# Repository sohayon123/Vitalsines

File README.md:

# Vitalsines
 
During my time as a co-op student at Vitalsines, I was responsible for the design and assembly of a variety of mechanical and electrical projects, however, the main project that I worked on was a device with the objective of measuring pulse wave velocity in a comfortable and easy way. 

## PCB Design
I developed 3 different PCBs for this project, one for filtering incoming data from piezo sensors of my design, one for aggregating sensor data lines, and one for sending this data to a DAQ. These PCBs were extremely small, at only 2cm diameter, and were assembled by hand. They contained a adjustable low pass filter to get rid of some of the noise in the analog signal from the piezo. The component size for this PCB was 0603 and the board was designed to have 4 layers, one ground plane and one 10V power plane, to help clean up the traces.

## Mechanical Design

The mechanical design involved creating a strap that would host all of the electronics and sit comfortably on the chest. It also involved the design of some enclosures for the piezo sensors. Below are some pictures of the final result and some of the CAD files. The strap was designed with some areas of varying thickness to allow the PCBs to clip directly into the prototype strap. There were some cavities left in the strap as well to accomodate the various sensor cables.

[Link to Cad Viewer!](https://github.com/sohayon123/Vitalsines/blob/main/CAD/strap.STL)

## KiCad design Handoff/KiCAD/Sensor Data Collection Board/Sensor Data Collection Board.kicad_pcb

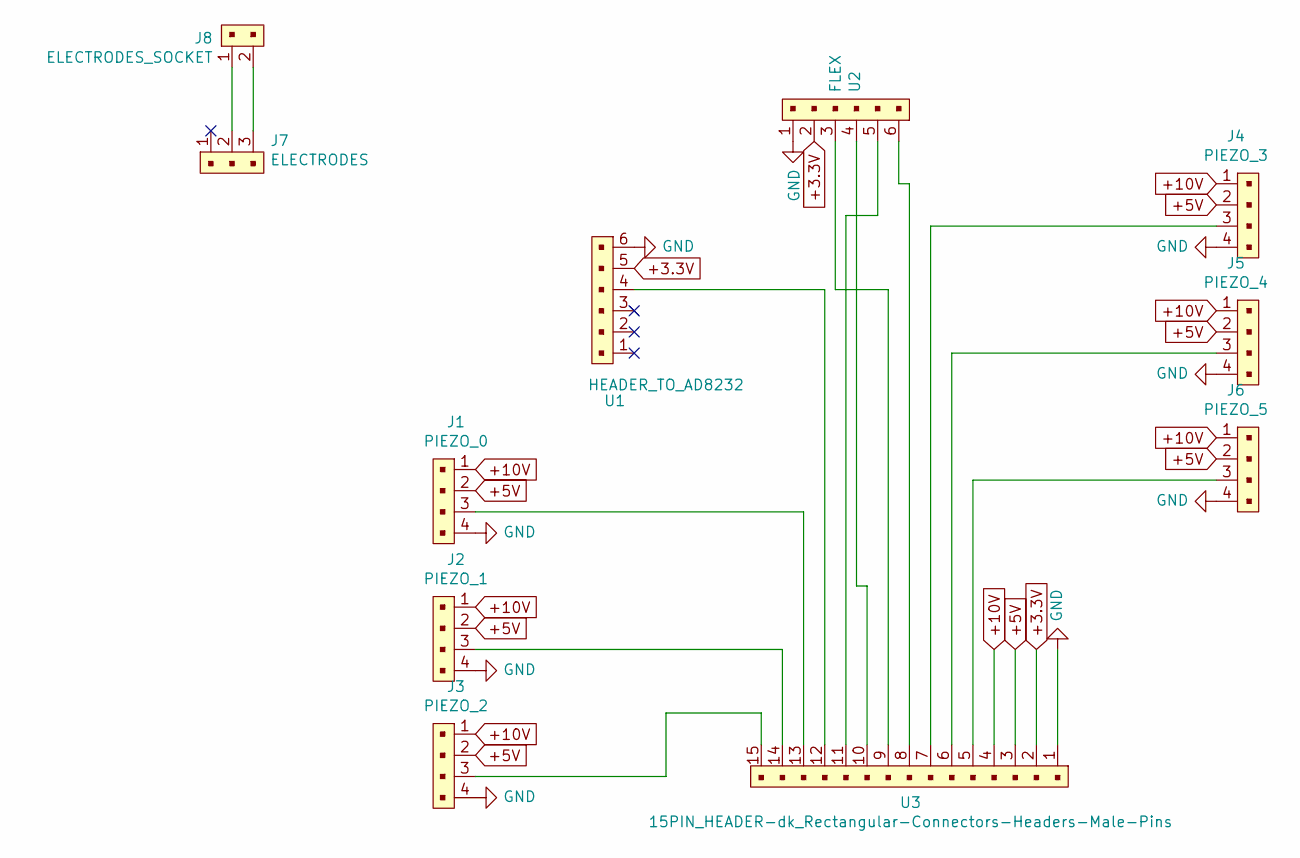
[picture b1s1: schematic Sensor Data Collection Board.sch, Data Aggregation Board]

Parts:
J1: PIEZO_0; BM04B-SRSS-TB; MPN B4B-PH-K-S(LF)(SN); Digi-Key_PN 455-1706-ND
J2: PIEZO_1; BM04B-SRSS-TB; MPN B4B-PH-K-S(LF)(SN); Digi-Key_PN 455-1706-ND
J3: PIEZO_2; BM04B-SRSS-TB; MPN B4B-PH-K-S(LF)(SN); Digi-Key_PN 455-1706-ND
J4: PIEZO_3; BM04B-SRSS-TB; MPN B4B-PH-K-S(LF)(SN); Digi-Key_PN 455-1706-ND
J5: PIEZO_4; BM04B-SRSS-TB; MPN B4B-PH-K-S(LF)(SN); Digi-Key_PN 455-1706-ND
J6: PIEZO_5; BM04B-SRSS-TB; MPN B4B-PH-K-S(LF)(SN); Digi-Key_PN 455-1706-ND
J7: ELECTRODES; PinHeader_1x03_P2.54mm_Vertical; MPN 640456-3; Digi-Key_PN A19470-ND
J8: ELECTRODES_SOCKET; SM02B-SRSS-TB; MPN 22-23-2021; Digi-Key_PN WM4200-ND
U1: HEADER_TO_AD8232; PinHeader_1x06_P2.54mm_Vertical
U2: FLEX; BM06B-SRSS-TB
U3: 15PIN_HEADER-dk_Rectangular-Connectors-Headers-Ma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; DB15 2 row

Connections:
+3.3V: U1.5, U2.2, U3.2
+5V: J1.2, J2.2, J3.2, J4.2, J5.2, J6.2, U3.3
+10V: J1.1, J2.1, J3.1, J4.1, J5.1, J6.1, U3.4
GND: J1.4, J2.4, J3.4, J4.4, J5.4, J6.4, U1.6, U2.1, U3.1
unnamed: J1.3, U3.13
unnamed: J2.3, U3.14
unnamed: J3.3, U3.15
unnamed: J4.3, U3.7
unnamed: J5.3, U3.6
unnamed: J6.3, U3.5
unnamed: J7.2, J8.1
unnamed: J7.3, J8.2
unnamed: U1.4, U3.12
unnamed: U2.3, U3.9
unnamed: U2.4, U3.10
unnamed: U2.5, U3.11
unnamed: U2.6, U3.8

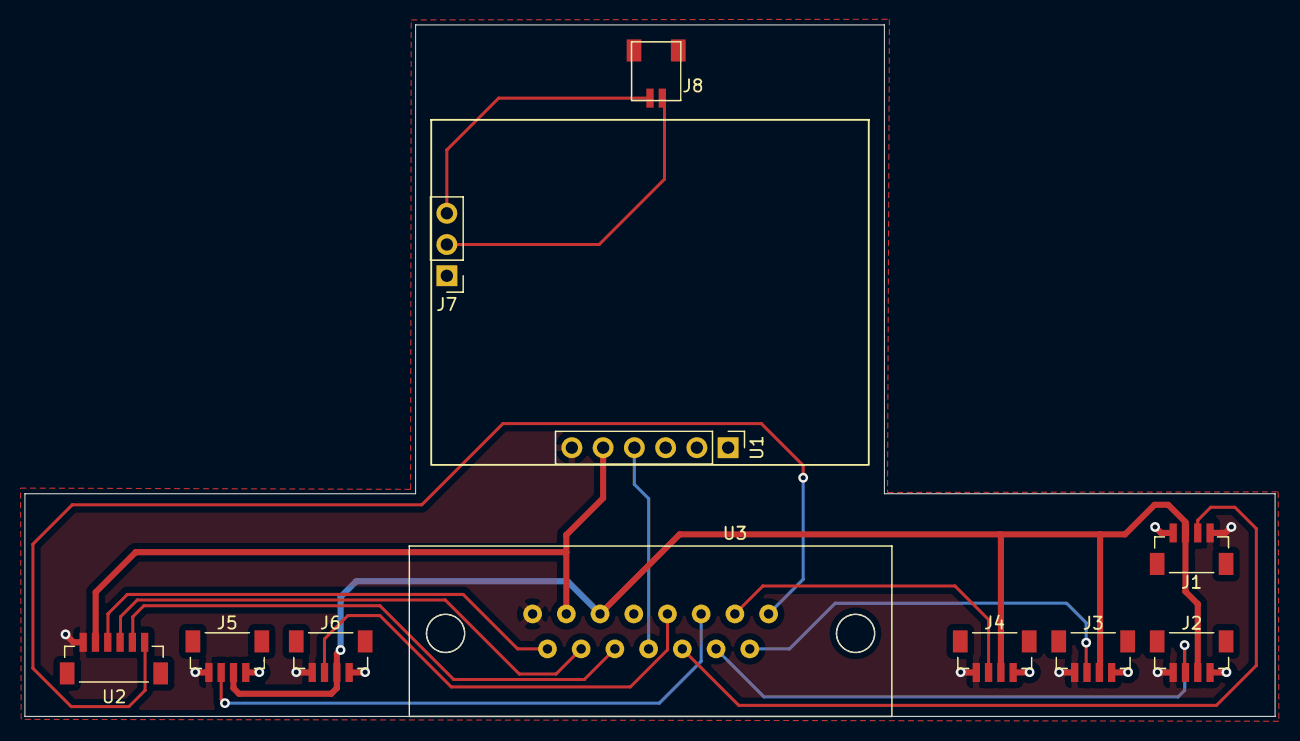
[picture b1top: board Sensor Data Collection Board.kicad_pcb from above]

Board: 4 copper layers, 101.6 x 56.2 mm, 11 parts (0 on the bottom side), 17 nets.

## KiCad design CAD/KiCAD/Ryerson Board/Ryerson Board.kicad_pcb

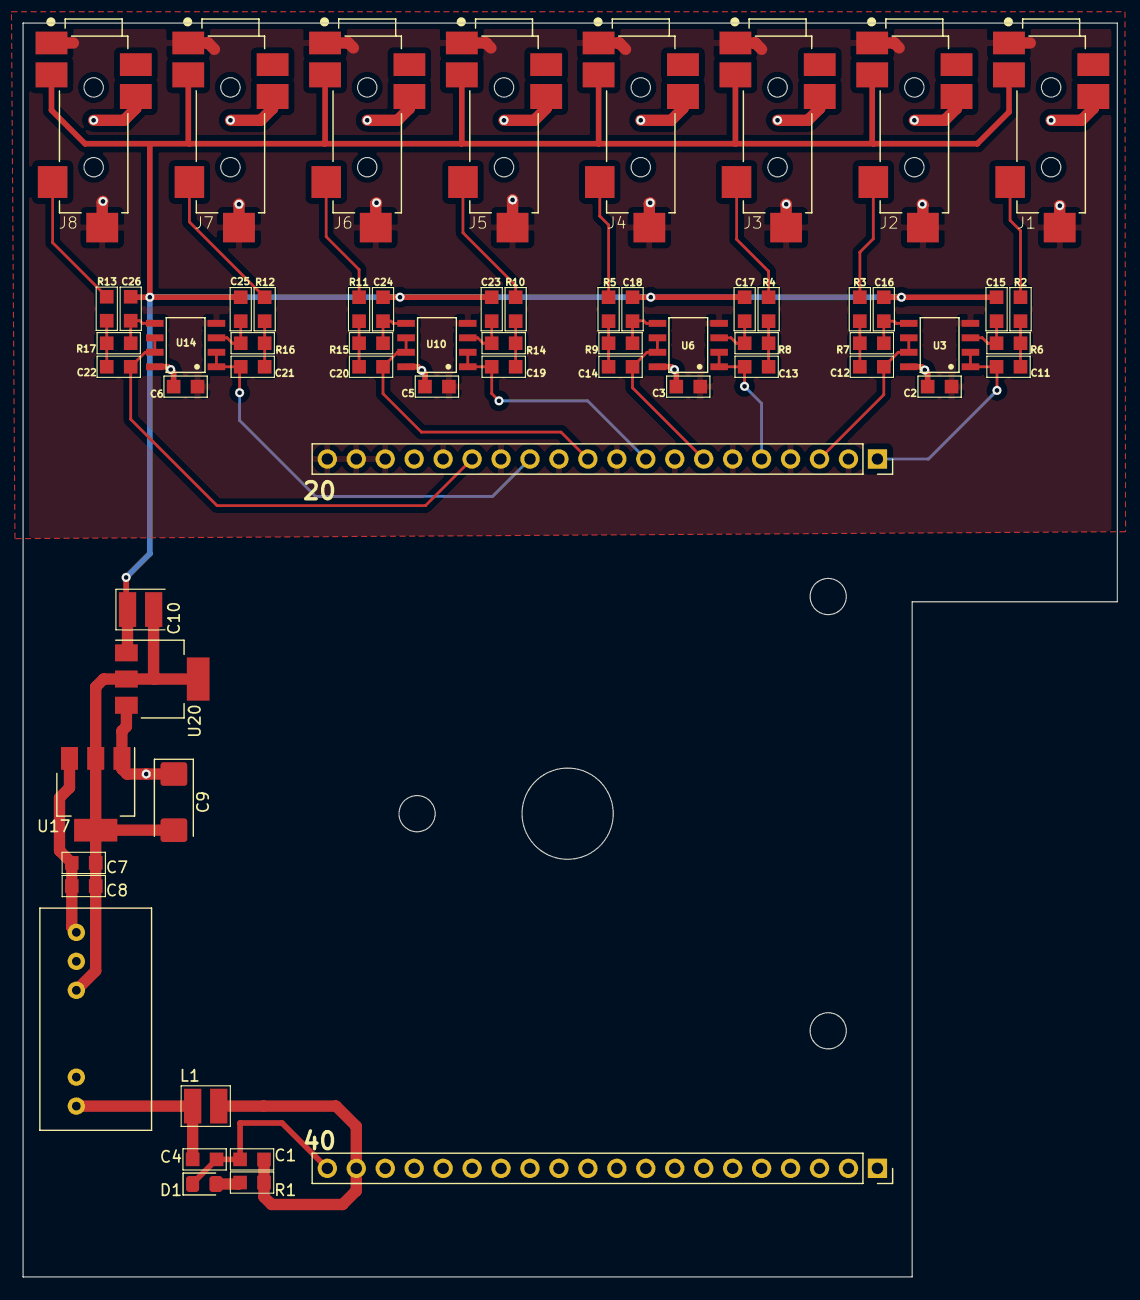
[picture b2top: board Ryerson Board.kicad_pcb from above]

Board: 4 copper layers, 96.0 x 110.0 mm, 62 parts (0 on the bottom side), 40 nets.

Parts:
C1, C4: 4.7uF/50V; 0805
C2, C3, C5, C6: 0.1uF; 0805
C7: 2.2uF; 0805
C8: 1uF; 0805
C9: 47uF/16V; CP_EIA-6032-28_Kemet-C
C10: 47uF/10V; 1210
C11, C12, C13, C14, C19, C20, C21, C22: 2nF; 0805
C15, C16, C17, C18, C23, C24, C25, C26: 1nF; 0805
D1: GREEN; LED_0805_2012Metric_Pad1.15x1.40mm_HandSolder
J1, J2, J3, J4, J5, J6, J7, J8: SJ-43516-SMT; CUI_SJ-43516-SMT
L1: 6.8uH; 1210
R1: 1k5; 0805
R2, R3, R4, R5, R10, R11, R12, R13: 5k23; 0805
R6, R7, R8, R9, R14, R15, R16, R17: 7k23; 0805
U3, U6, U10, U14: LMC6062; LMC6062IMX
U11: MDS01L-12; SIP-7
U17: MCP1804x-A002xDB; SOT-223-3_TabPin2
U20: MCP1804x-5002xDB; SOT-223-3_TabPin2
U23: 1-20; PinSocket_1x20_P2.54mm_Vertical
U26: 21-40; PinSocket_1x20_P2.54mm_Vertical

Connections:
5V_IN: C1.1, L1.2, R1.1, U26.19
+5V: C10.1, C15.2, C16.2, C17.2, C18.2, C23.2, C24.2, C25.2, C26.2, J1.4, J2.4, J3.4, J4.4, J5.4, J6.4, J7.4, J8.4, U20.1
+10V: C2.1, C3.1, C5.1, C6.1, C9.1, J1.3, J2.3, J3.3, J4.3, J5.3, J6.3, J7.3, J8.3, U3.8, U6.8, U10.8, U14.8, U17.1, U20.3
AGND: C2.2, C3.2, C5.2, C6.2, C7.2, C8.2, C9.2, C10.2, J1.1, J1.5, J2.1, J2.5, J3.1, J3.5, J4.1, J4.5, J5.1, J5.5, J6.1, J6.5, J7.1, J7.5, J8.1, J8.5, U3.4, U6.4, U10.4, U11.4, U14.4, U17.2, U20.2, U23.2, U23.4, U23.6, U23.8, U23.10, U23.12, U23.14, U23.16, U23.18, U23.19, U23.20
CH0: C11.1, U3.1, U3.2, U23.1
CH1: C12.1, U3.6, U3.7, U23.3
CH2: C13.1, U6.1, U6.2, U23.5
CH3: C14.1, U6.6, U6.7, U23.7
CH4: C19.1, U10.1, U10.2, U23.9
CH5: C20.1, U10.6, U10.7, U23.11
CH6: C21.1, U14.1, U14.2, U23.13
CH7: C22.1, U14.6, U14.7, U23.15
DGND: C1.2, C4.2, D1.1, U11.2, U26.2, U26.4, U26.6, U26.8, U26.10, U26.12, U26.14, U26.20
unnamed: C4.1, L1.1, U11.1
unnamed: C7.1, C8.1, U11.5, U17.3
unnamed: C11.2, R2.1, R6.2
unnamed: C12.2, R3.1, R7.2
unnamed: C13.2, R4.1, R8.2
unnamed: C14.2, R5.1, R9.2
unnamed: C15.1, R6.1, U3.3
unnamed: C16.1, R7.1, U3.5
unnamed: C17.1, R8.1, U6.3
unnamed: C18.1, R9.1, U6.5
unnamed: C19.2, R10.1, R14.2
unnamed: C20.2, R11.1, R15.2
unnamed: C21.2, R12.1, R16.2
unnamed: C22.2, R13.1, R17.2
unnamed: C23.1, R14.1, U10.3
unnamed: C24.1, R15.1, U10.5
unnamed: C25.1, R16.1, U14.3
unnamed: C26.1, R17.1, U14.5
unnamed: D1.2, R1.2
unnamed: J1.2, R2.2
unnamed: J2.2, R3.2
unnamed: J3.2, R4.2
unnamed: J4.2, R5.2
unnamed: J5.2, R10.2
unnamed: J6.2, R11.2
unnamed: J7.2, R12.2
unnamed: J8.2, R13.2

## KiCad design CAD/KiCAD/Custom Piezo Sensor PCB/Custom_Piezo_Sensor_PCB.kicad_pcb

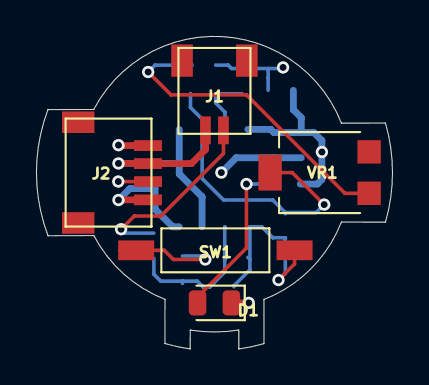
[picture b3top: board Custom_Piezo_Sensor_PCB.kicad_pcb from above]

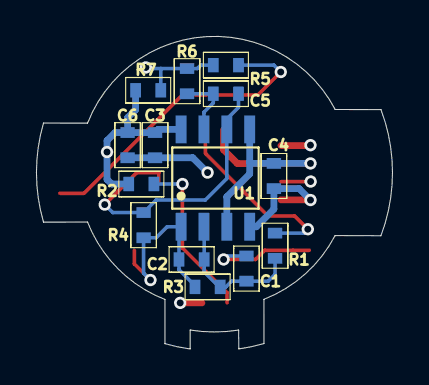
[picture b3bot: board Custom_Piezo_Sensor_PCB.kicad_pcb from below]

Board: 4 copper layers, 19.8 x 17.4 mm, 19 parts (14 on the bottom side), 12 nets.

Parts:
C1: 47nF; 0603
C2: 360pF; 0603
C3, C4: 10uF; 0603
C5: 20pF; 0603
C6: 0.1uF; 0603
D1: LED; LED_0805_2012Metric
J1: PIEZO_INPUT; SM02B-SRSS-TB
J2: PCB_TO_JACK; SM04B-SRSS-TB
R1, R7: 1M; 0603
R2: 3K9; 0603
R3: 22M; 0603
R4, R5: 10k; 0603
R6: 20R; 0603
SW1: SW_DIP_x01; EDS01SGNNTR04Q
U1: LMC6062; LMC6062IMX
VR1: 1M; 3314G-1-105E

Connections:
+5V: C4.2, J1.2, J2.2, U1.3, U1.5
+10V: C3.2, C6.1, J2.1, R2.2, R7.2, U1.8
GND: C3.1, C4.1, C6.2, D1.1, J2.4, U1.4
unnamed: C1.1, SW1.1
unnamed: C1.2, C2.2, R1.1, R3.2, U1.2
unnamed: C2.1, R3.1, R4.2, SW1.2, U1.1
unnamed: C5.1, R6.2, U1.7
unnamed: C5.2, R4.1, U1.6, VR1.1
unnamed: D1.2, R2.1
unnamed: J1.1, R1.2
unnamed: J2.3, R5.1, R6.1, R7.1
unnamed: R5.2, VR1.3

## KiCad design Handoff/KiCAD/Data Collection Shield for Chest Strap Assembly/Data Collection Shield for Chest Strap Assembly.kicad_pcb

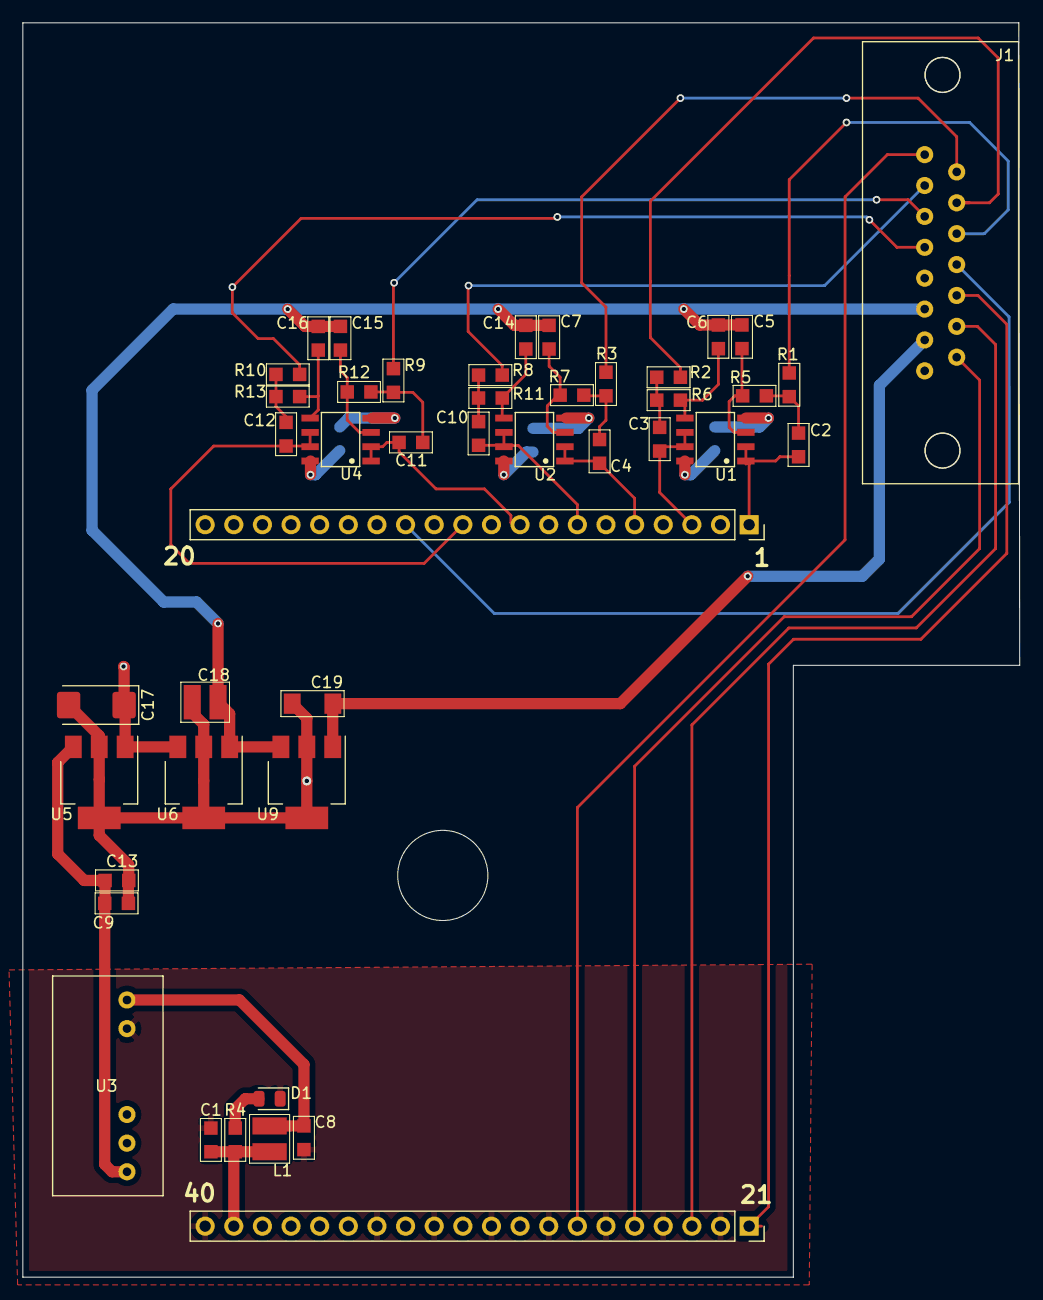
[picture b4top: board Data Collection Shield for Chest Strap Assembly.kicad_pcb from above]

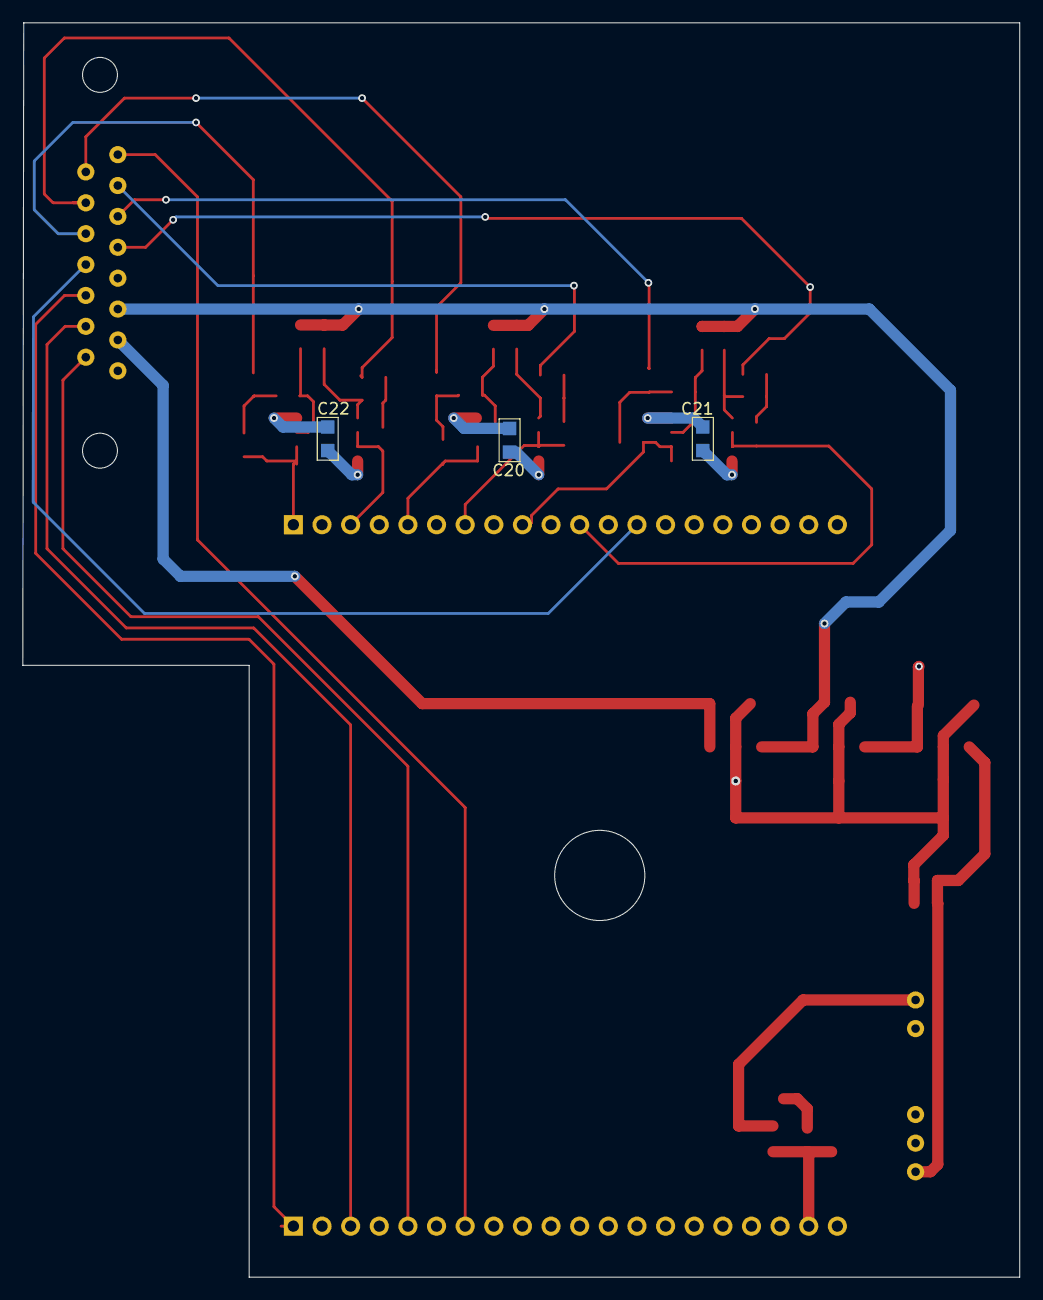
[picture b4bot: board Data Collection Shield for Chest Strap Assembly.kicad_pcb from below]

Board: 4 copper layers, 88.4 x 111.3 mm, 47 parts (3 on the bottom side), 38 nets.

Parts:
C1, C8: 4.7uF/25V; 0805
C2, C3, C4, C10, C11, C12: 2nF; 0805
C5, C6, C7, C14, C15, C16: 1nF; 0805
C9: 2.2uF; 0805
C13: 1uF; 0805
C17: 47uF/16V; CP_EIA-6032-28_Kemet-C
C18: 47uF/10V; 1210
C19: 10uF/10V; 1206
C20, C21, C22: 0.1uF; 0805
D1: GRN; LED_0805_2012Metric
J1: 15PIN_HEADER; DB15 2 row
L1: 6.8uH; 1210
R1, R2, R3, R8, R9, R10: 5k23; 0805
R4: 1k5; 0805
R5, R6, R7, R11, R12, R13: 7k32; 0805
U1, U2, U4: LMC6062; LMC6062IMX
U3: MDS01L-12; SIP-7
U5: MCP1804x-A002xDB; SOT-223-3_TabPin2
U6: MCP1804x-5002xDB; SOT-223-3_TabPin2
U8: PINS 21 - 40 DAQ; PinSocket_1x20_P2.54mm_Vertical
U9: MCP1804x-3302xDB; SOT-223-3_TabPin2
U10: PINS 1 - 20 DAQ; PinSocket_1x20_P2.54mm_Vertical

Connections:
3.3V: C19.1, J1.2, U9.1
5V: C5.2, C6.2, C7.2, C14.2, C15.2, C16.2, C18.1, J1.3, U6.1, U9.3
5V_IN: C1.1, L1.1, R4.1, U8.19
10V: C17.1, C20.1, C21.1, C22.1, J1.4, U1.8, U2.8, U4.8, U5.1, U6.3
AGND: C9.2, C13.2, C17.2, C18.2, C19.2, C20.2, C21.2, C22.2, J1.1, U1.4, U2.4, U3.4, U4.4, U5.2, U6.2, U9.2, U10.2, U10.4, U10.6, U10.8, U10.10, U10.12, U10.14, U10.16, U10.18, U10.19, U10.20
CH0: C2.1, U1.1, U1.2, U10.1
CH1: C3.1, U1.6, U1.7, U10.3
CH2: C4.1, U2.1, U2.2, U10.5
CH3: C10.1, U2.6, U2.7, U10.7
CH4: C11.1, U4.1, U4.2, U10.9
CH5: C12.1, U4.6, U4.7, U10.11
CH6: J1.12, U10.13
DGND: C1.2, C8.2, D1.1, U3.2, U8.2, U8.4, U8.6, U8.8, U8.10, U8.12, U8.14, U8.20
FLEX_SCL: J1.11, U8.1
FLEX_SDA: J1.10, U8.3
FLEX_nDRDY: J1.9, U8.5
FLEX_nRST: J1.8, U8.7
unnamed: C2.2, R1.1, R5.2
unnamed: C3.2, R2.1, R6.2
unnamed: C4.2, R3.1, R7.2
unnamed: C5.1, R5.1, U1.3
unnamed: C6.1, R6.1, U1.5
unnamed: C7.1, R7.1, U2.3
unnamed: C8.1, L1.2, U3.1
unnamed: C10.2, R8.1, R11.2
unnamed: C11.2, R9.1, R12.2
unnamed: C12.2, R10.1, R13.2
unnamed: C9.1, C13.1, U3.5, U5.3
unnamed: C14.1, R11.1, U2.5
unnamed: C15.1, R12.1, U4.3
unnamed: C16.1, R13.1, U4.5
unnamed: D1.2, R4.2
SIG_IN0: J1.13, R1.2
SIG_IN1: J1.14, R2.2
SIG_IN2: J1.15, R3.2
SIG_IN3: J1.7, R8.2
SIG_IN4: J1.6, R9.2
SIG_IN5: J1.5, R10.2

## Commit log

2021-07-08 init
